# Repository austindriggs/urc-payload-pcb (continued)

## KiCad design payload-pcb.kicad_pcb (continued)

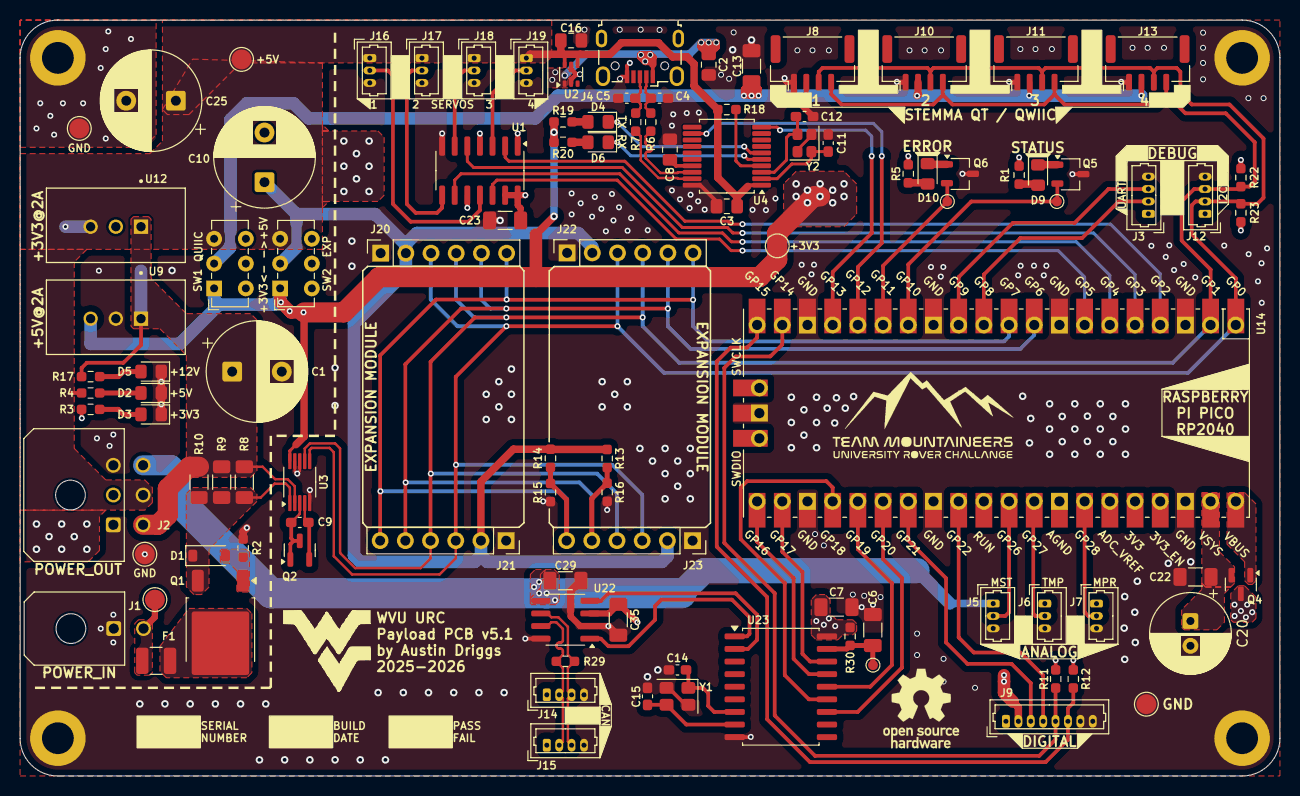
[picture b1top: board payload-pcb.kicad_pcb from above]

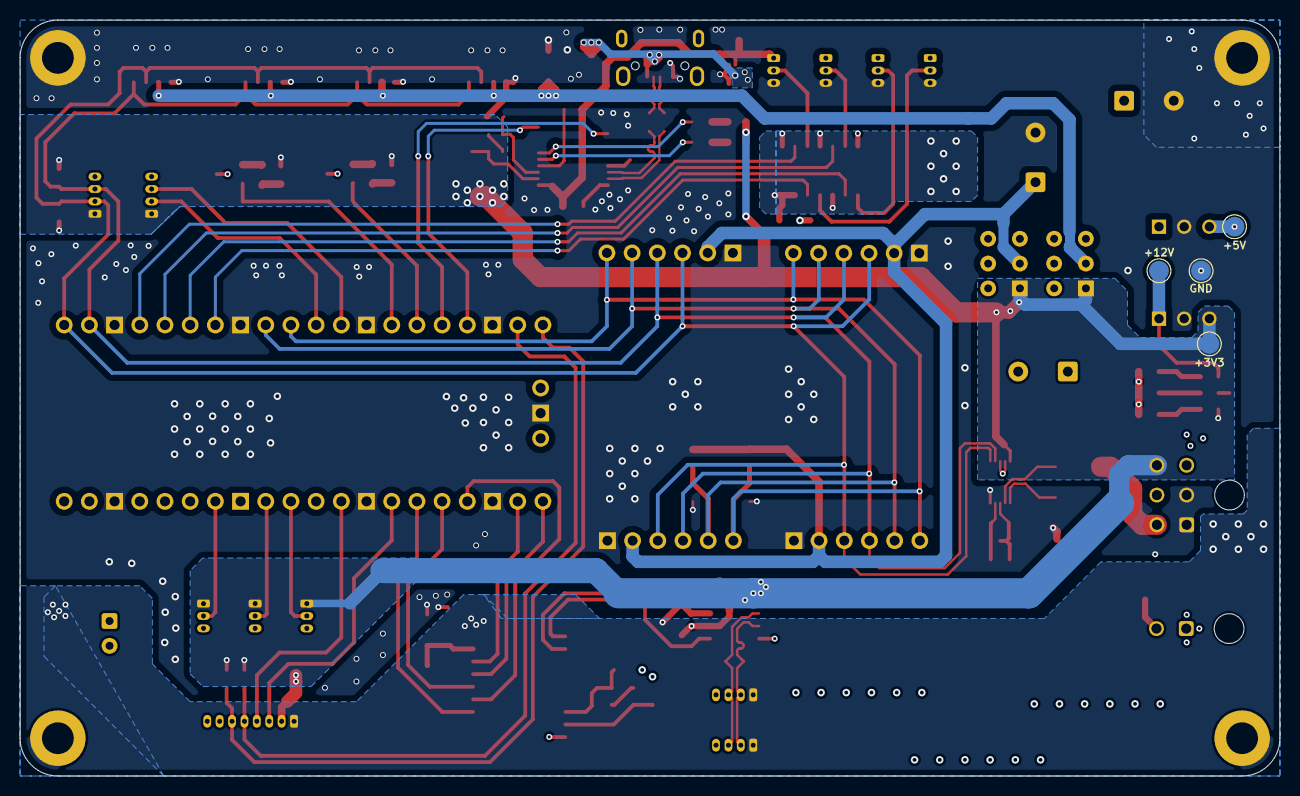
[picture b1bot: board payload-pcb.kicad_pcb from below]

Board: 4 copper layers, 127.0 x 76.2 mm, 113 parts (4 on the bottom side), 71 nets.

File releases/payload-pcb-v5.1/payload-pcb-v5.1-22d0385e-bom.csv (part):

"Reference","Value","DNP","Footprint","Datasheet","Description","Vendor","Vendor Part Number","Manufacturer","Manufacturer Part Number","Qty","Notes","Comments"
"C1,C10,C25","1000uF","","Capacitor_THT:CP_Radial_D10.0mm_P5.00mm","https://www.nichicon.co.jp/english/series_items/catalog_pdf/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","CAP ALUM 1000UF 20% 25V RADIAL","Digikey","493-1065-ND","Nichicon","UVR1E102MPD","3","",""
"C2,C3,C6,C7,C8,C22,C23,C29,C35","0.1uF","","Capacitor_SMD:C_1206_3216Metric_Pad1.33x1.80mm_HandSolder","https://www.yageogroup.com/content/datasheet/asset/file/KEM_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","CAP CER 0.1UF 50V X7R 1206","Digikey","399-C1206C104J5RACTUCT-ND","KEMET","C1206C104J5RACTU","9","",""
"C4,C5","47p","","Capacitor_SMD:C_0603_1608Metric_Pad1.08x0.95mm_HandSolder","https://www.yageogroup.com/content/datasheet/asset/file/KEM_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","CAP CER 47PF 50V X7R 0603","Digikey","399-C0603C470K5RACTUCT-ND","KEMET","C0603C470K5RACTU","2","",""
"C9","470pF","","Capacitor_SMD:C_0603_1608Metric_Pad1.08x0.95mm_HandSolder","https://www.yageogroup.com/content/datasheet/asset/file/KEM_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","CAP CER 470PF 50V X7R 0603","Digikey","399-C0603C471K5RACTUCT-ND","KEMET","C0603C471K5RACTU","1","",""
"C20","10uF","","Capacitor_THT:CP_Radial_D8.0mm_P2.50mm","https://www.nichicon.co.jp/english/series_items/catalog_pdf/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","CAP ALUM 10UF 20% 160V RADIAL TH","Digikey","493-12828-1-ND","Nichicon","UVR2C100MPD1TD","1","",""
"C30,C31","22pF","","Capacitor_SMD:C_0603_1608Metric_Pad1.08x0.95mm_HandSolder","https://www.yageogroup.com/content/datasheet/asset/file/KEM_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","CAP CER 22PF 50V X7R 0603","Digikey","399-C0603C220K5RACTUCT-ND","KEMET","C0603C220K5RACTU","2","",""
"D1","BZT52C10-TP","","Diode_SMD:D_SOD-123","https://www.mccsemi.com/pdf/Products/BZT52C2V0_BZT52C75(500m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","DIODE ZENER 10V 500MW SOD123","Digikey","BZT52C10-TPMSCT-ND","MCC (Micro Commercial Components)","BZT52C10-TP","1","",""
"D2","+5V","","LED_SMD:LED_0805_2012Metric_Pad1.15x1.40mm_HandSolder","https://www.we-online.com/components/products/datasheet/1500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","LED GREEN CLEAR 0805 SMD","Digikey","732-4983-1-ND","Würth Elektronik","150080GS75000","1","",""
"D3","+3V3","","LED_SMD:LED_0805_2012Metric_Pad1.15x1.40mm_HandSolder","https://www.we-online.com/components/products/datasheet/1500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","LED GREEN CLEAR 0805 SMD","Digikey","732-4983-1-ND","Würth Elektronik","150080GS75000","1","",""
"D5","+12V","","LED_SMD:LED_0805_2012Metric_Pad1.15x1.40mm_HandSolder","https://www.we-online.com/components/products/datasheet/1500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","LED GREEN CLEAR 0805 SMD","Digikey","732-4983-1-ND","Würth Elektronik","150080GS75000","1","",""
"D9","STATUS","","LED_SMD:LED_0805_2012Metric_Pad1.15x1.40mm_HandSolder","https://www.we-online.com/components/products/datasheet/1500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","LED BLUE CLEAR 0805 SMD","Digikey","732-4982-1-ND","Würth Elektronik","150080BS75000","1","",""
"D10","ERROR","","LED_SMD:LED_0805_2012Metric_Pad1.15x1.40mm_HandSolder","https://www.we-online.com/components/products/datasheet/1500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","LED RED CLEAR 0805 SMD","Digikey","732-4984-1-ND","Würth Elektronik","150080RS75000","1","",""
"F1","PTC","","Fuse:Fuse_1210_3225Metric","https://www.littelfuse.com/assetdocs/1210l-datasheet-update?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","PTC RESET FUSE 16V 1.5A 1210","Digikey","F6135CT-ND","Littelfuse Inc.","1210L150/16WR","1","",""
"H1,H2,H3,H4","MountingHole","","MountingHole:MountingHole_3.2mm_M3_DIN965_Pad","~","","","","","","4","",""
"J1","POWER_IN","","Connector_Molex:Molex_Micro-Fit_3.0_43045-0200_2x01_P3.00mm_Horizontal","https://tools.molex.com/pdm_docs/ps/PS-43045.pdf","CONN HEADER R/A 2POS","Digikey","WM1813-ND","Molex","0430450200","1","",""
"J2","POWER_OUT","","Connector_Molex:Molex_Micro-Fit_3.0_43045-0600_2x03_P3.00mm_Horizontal","https://tools.molex.com/pdm_docs/ps/PS-43045.pdf","CONN HEADER R/A 6POS 3MM","Digikey","WM1821-ND","Molex","0430450602","1","",""
"J3","UART","DNP","Connector_Molex:Molex_PicoBlade_53047-0410_1x04_P1.25mm_Vertical","https://www.molex.com/pdm_docs/sd/530470310_sd.pdf","CONN HEADER VERT 4POS 1.25MM","Digikey","WM1733-ND","Molex","0530470410","1","",""
"J4","USB","","Connector_USB:USB_Micro-B_Wuerth_629105150521","https://www.we-online.com/components/products/datasheet/6291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","CONN RCPT USB2.0 MICRO B SMD R/A","Digikey","732-5960-1-ND","Würth Elektronik","629105150521","1","",""
"J5","MST","","Connector_Molex:Molex_PicoBlade_53047-0310_1x03_P1.25mm_Vertical","https://www.molex.com/pdm_docs/sd/530470310_sd.pdf","CONN HEADER VERT 3POS 1.25MM","Digikey","WM1732-ND","Molex","0530470310","1","",""
"J6","TMP","","Connector_Molex:Molex_PicoBlade_53047-0310_1x03_P1.25mm_Vertical","https://www.molex.com/pdm_docs/sd/530470310_sd.pdf","CONN HEADER VERT 3POS 1.25MM","Digikey","WM1732-ND","Molex","0530470310","1","",""
"J7","MPR","","Connector_Molex:Molex_PicoBlade_53047-0310_1x03_P1.25mm_Vertical","https://www.molex.com/pdm_docs/sd/530470310_sd.pdf","CONN HEADER VERT 3POS 1.25MM","Digikey","WM1732-ND","Molex","0530470310","1","",""
"J8","QWIIC4","","Connector_JST:JST_GH_BM04B-GHS-TBT_1x04-1MP_P1.25mm_Vertical","https://www.jst-mfg.com/product/pdf/eng/eGH.pdf","CONN HEADER SMD R/A 4POS 1.25MM","Digikey","SM04B-GHS-TB","JST Sales America Inc.","455-1566-1-ND","1","",""
"J9","DIGITAL","","Connector_Molex:Molex_PicoBlade_53047-0810_1x08_P1.25mm_Vertical","https://www.molex.com/pdm_docs/sd/530470310_sd.pdf","CONN HEADER VERT 8POS 1.25MM","Digikey","WM1737-ND","Molex","0530470810","1","",""
"J10","QWIIC3","","Connector_JST:JST_GH_BM04B-GHS-TBT_1x04-1MP_P1.25mm_Vertical","https://www.jst-mfg.com/product/pdf/eng/eGH.pdf","CONN HEADER SMD R/A 4POS 1.25MM","Digikey","SM04B-GHS-TB","JST Sales America Inc.","455-1566-1-ND","1","",""
"J11","QWIIC2","","Connector_JST:JST_GH_BM04B-GHS-TBT_1x04-1MP_P1.25mm_Vertical","https://www.jst-mfg.com/product/pdf/eng/eGH.pdf","CONN HEADER SMD R/A 4POS 1.25MM","Digikey","SM04B-GHS-TB","JST Sales America Inc.","455-1566-1-ND","1","",""
"J12","I2C","DNP","Connector_Molex:Molex_PicoBlade_53047-0410_1x04_P1.25mm_Vertical","https://www.molex.com/pdm_docs/sd/530470310_sd.pdf","CONN HEADER VERT 4POS 1.25MM","Digikey","WM1733-ND","Molex","0530470410","1","",""
"J13","QWIIC1","","Connector_JST:JST_GH_BM04B-GHS-TBT_1x04-1MP_P1.25mm_Vertical","https://www.jst-mfg.com/product/pdf/eng/eGH.pdf","CONN HEADER SMD R/A 4POS 1.25MM","Digikey","SM04B-GHS-TB","JST Sales America Inc.","455-1566-1-ND","1","",""
"J14,J15","CAN","","Connector_Molex:Molex_PicoBlade_53047-0410_1x04_P1.25mm_Vertical","https://www.molex.com/pdm_docs/sd/530470310_sd.pdf","CONN HEADER VERT 4POS 1.25MM","Digikey","WM1733-ND","Molex","0530470410","2","",""
"J16","SERVO4","","Connector_Molex:Molex_PicoBlade_53047-0310_1x03_P1.25mm_Vertical","https://www.molex.com/pdm_docs/sd/530470310_sd.pdf","CONN HEADER VERT 3POS 1.25MM","Digikey","WM1732-ND","Molex","0530470310","1","",""
"J17","SERVO3","","Connector_Molex:Molex_PicoBlade_53047-0310_1x03_P1.25mm_Vertical","https://www.molex.com/pdm_docs/sd/530470310_sd.pdf","CONN HEADER VERT 3POS 1.25MM","Digikey","WM1732-ND","Molex","0530470310","1","",""
"J18","MANIPULATOR","","Connector_Molex:Molex_PicoBlade_53047-0310_1x03_P1.25mm_Vertical","https://www.molex.com/pdm_docs/sd/530470310_sd.pdf","CONN HEADER VERT 3POS 1.25MM","Digikey","WM1732-ND","Molex","0530470310","1","",""
"J19","SCOOP","","Connector_Molex:Molex_PicoBlade_53047-0310_1x03_P1.25mm_Vertical","https://www.molex.com/pdm_docs/sd/530470310_sd.pdf","CONN HEADER VERT 3POS 1.25MM","Digikey","WM1732-ND","Molex","0530470310","1","",""
"J20","EXP1","","Connector_PinSocket_2.54mm:PinSocket_1x06_P2.54mm_Vertical","https://mm.digikey.com/Volume0/opasdata/d220001/medias/docus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","CONN RCPT 6POS 0.1 GOLD PCB","Digikey","SAM10025-ND","Samtec Inc.","SAM10025-ND","1","",""
"J21","EXP2","","Connector_PinSocket_2.54mm:PinSocket_1x06_P2.54mm_Vertical","https://mm.digikey.com/Volume0/opasdata/d220001/medias/docus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","CONN RCPT 6POS 0.1 GOLD PCB","Digikey","SAM10025-ND","Samtec Inc.","SAM10025-ND","1","",""
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
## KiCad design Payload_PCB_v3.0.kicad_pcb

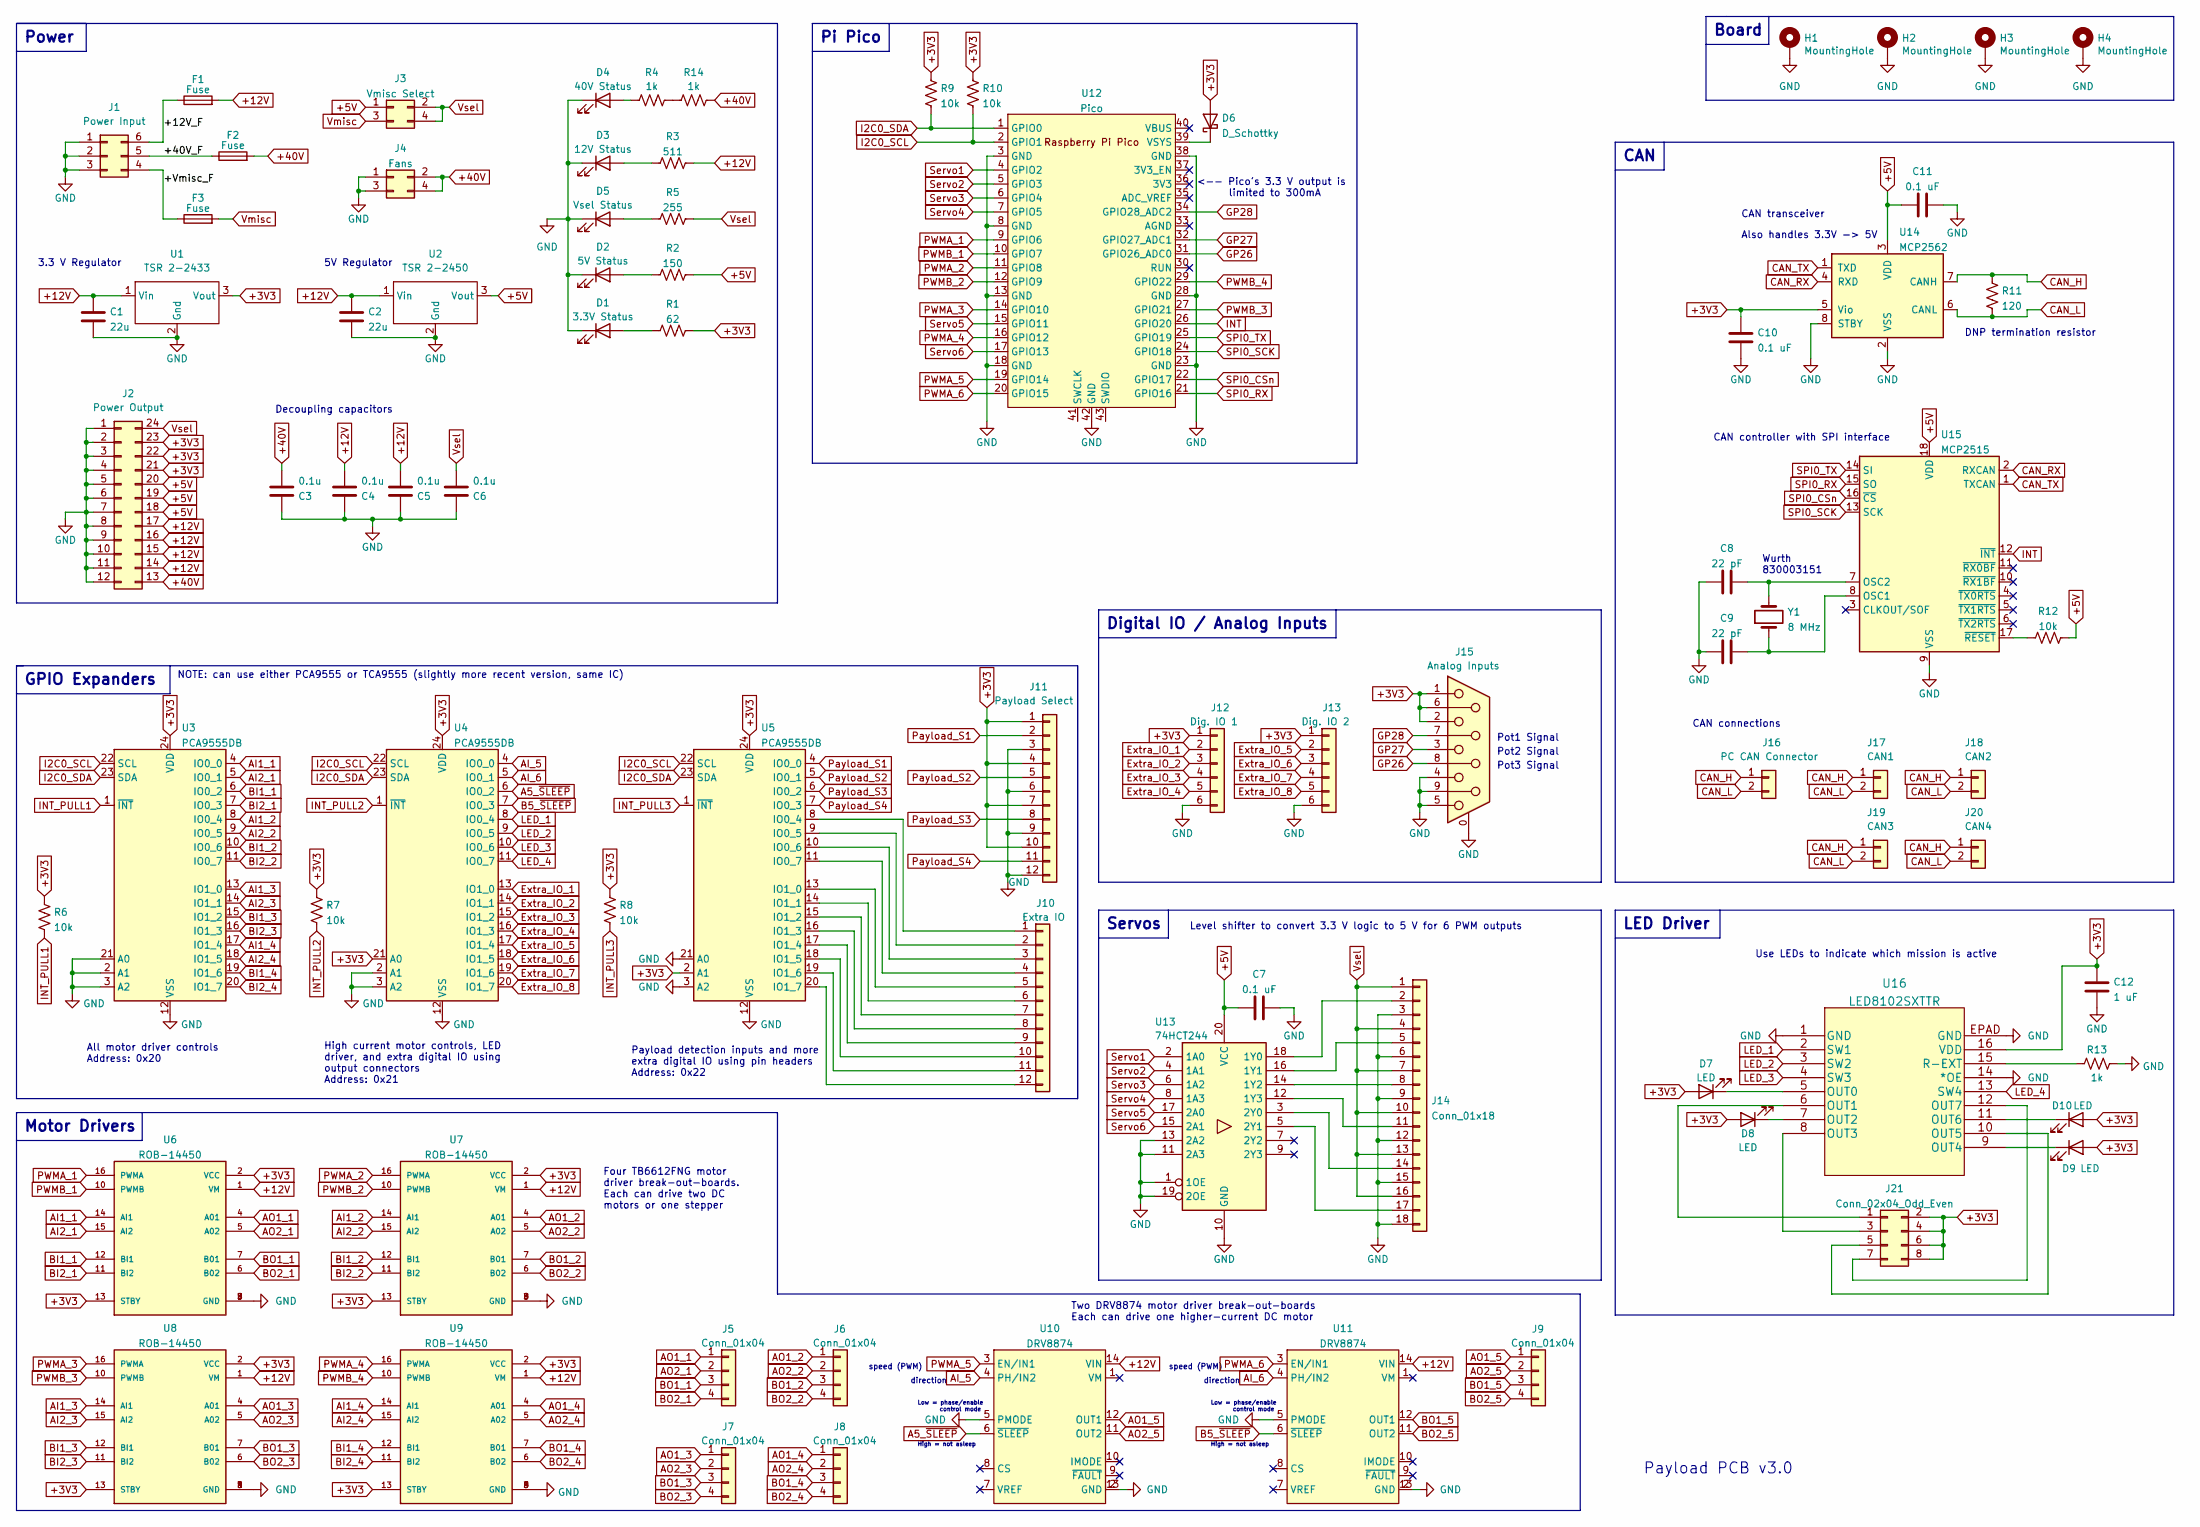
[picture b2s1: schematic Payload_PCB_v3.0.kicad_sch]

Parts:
C1, C2: 22u; UCM1H220MCL1GS
C3, C4, C5, C6: 0.1u; C_1206_3216Metric_Pad1.33x1.80mm_HandSolder
C7, C10, C11: 0.1 uF; C_1206_3216Metric_Pad1.33x1.80mm_HandSolder
C8, C9: 22 pF; C_0603_1608Metric_Pad1.08x0.95mm_HandSolder
C12: 1 uF; C_1206_3216Metric_Pad1.33x1.80mm_HandSolder
D1: 3.3V Status; LED_0805_2012Metric_Pad1.15x1.40mm_HandSolder
D2: 5V Status; LED_0805_2012Metric_Pad1.15x1.40mm_HandSolder
D3: 12V Status; LED_0805_2012Metric_Pad1.15x1.40mm_HandSolder
D4: 40V Status; LED_0805_2012Metric_Pad1.15x1.40mm_HandSolder
D5: Vsel Status; LED_0805_2012Metric_Pad1.15x1.40mm_HandSolder
D6: D_Schottky; D_SOD-323_HandSoldering
D7, D8, D9, D10: LED; LED_0805_2012Metric_Pad1.15x1.40mm_HandSolder
F1, F2, F3: Fuse; Fuseholder_Blade_Mini_Keystone_3568
H1, H2, H3, H4: MountingHole; MountingHole_3.2mm_M3_DIN965_Pad
J1: Power Input; Molex_Mini-Fit_Jr_5569-06A2_2x03_P4.20mm_Horizontal
J2: Power Output; Molex_Mini-Fit_Jr_5569-24A2_2x12_P4.20mm_Horizontal
J3: Vmisc Select; PinHeader_2x02_P2.54mm_Vertical
J4: Fans; PinHeader_2x02_P2.54mm_Vertical
J5, J6, J7, J8, J9: Conn_01x04; PhoenixContact_MCV_1,5_4-G-3.5_1x04_P3.50mm_Vertical
J10: Extra IO; PinSocket_2x06_P2.54mm_Vertical
J11: Payload Select; SAMTEC_TSW-104-07-T-T
J12: Dig. IO 1; Molex_PicoBlade_53048-0610_1x06_P1.25mm_Horizontal
J13: Dig. IO 2; Molex_PicoBlade_53048-0610_1x06_P1.25mm_Horizontal
J14: Conn_01x18; SAMTEC_TSW-106-07-S-T
J15: Analog Inputs; DSUB-9_Female_Horizontal_P2.77x2.84mm_EdgePinOffset7.70mm_H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
J16: PC CAN Connector; 0393570002
J17: CAN1; 0393570002
J18: CAN2; 0393570002
J19: CAN3; 0393570002
J20: CAN4; 0393570002
J21: Conn_02x04_Odd_Even; PinHeader_2x04_P2.54mm_Vertical_SMD
R1: 62; R_0805_2012Metric_Pad1.20x1.40mm_HandSolder
R2: 150; R_0805_2012Metric_Pad1.20x1.40mm_HandSolder
R3: 511; R_0805_2012Metric_Pad1.20x1.40mm_HandSolder
R4, R13, R14: 1k; R_0805_2012Metric_Pad1.20x1.40mm_HandSolder
R5: 255; R_0805_2012Metric_Pad1.20x1.40mm_HandSolder
R6, R7, R8, R9, R10, R12: 10k; R_0805_2012Metric_Pad1.20x1.40mm_HandSolder
R11: 120; R_Axial_DIN0207_L6.3mm_D2.5mm_P10.16mm_Horizontal
U1: TSR 2-2433; CONV_TSR_2-2433
U2: TSR 2-2450; CONV_TSR_2-2433
U3, U4, U5: PCA9555DB; SSOP-24_3.9x8.7mm_P0.635mm
U6, U7, U8, U9: ROB-14450; MODULE_ROB-14450; PARTREV 11-13-17
U10, U11: DRV8874
U12: Pico; RPi_Pico_SMD_TH
U13: 74HCT244; SO-20_12.8x7.5mm_P1.27mm
U14: MCP2562; SOIC-8_3.9x4.9mm_P1.27mm
U15: MCP2515; SOIC-18W_7.5x11.6mm_P1.27mm
U16: LED8102SXTTR
Y1: 8 MHz; Crystal_SMD_HC49-SD

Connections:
+3V3: C10.1, C12.1, D6.2 (A), D7.2 (A), D8.2 (A), D9.2 (A), D10.2 (A), J2.21, J2.22, J2.23, J11.1, J11.4, J11.7, J11.10, J12.1, J13.1, J15.1, J15.2, J15.6, J21.2, J21.4, J21.6, J21.8, R1.2, R6.2, R7.2, R8.2, R9.2, R10.2, U1.3 (Vout), U3.24 (VDD), U4.21 (A0), U4.24 (VDD), U5.2 (A1), U5.24 (VDD), U6.2 (VCC), U6.13 (STBY), U7.2 (VCC), U7.13 (STBY), U8.2 (VCC), U8.13 (STBY), U9.2 (VCC), U9.13 (STBY), U14.5 (Vio), U16.16 (VDD)
+5V: C7.1, C11.1, J2.18, J2.19, J2.20, J3.1, R2.2, R12.2, U2.3 (Vout), U13.20 (VCC), U14.3 (VDD), U15.18 (VDD)
+12V: C1.1, C2.1, C4.2, C5.2, F1.2, J2.14, J2.15, J2.16, J2.17, R3.2, U1.1 (Vin), U2.1 (Vin), U6.1 (VM), U7.1 (VM), U8.1 (VM), U9.1 (VM), U10.14 (VIN), U11.14 (VIN)
+40V: C3.2, F2.2, J2.13, J4.2, J4.4, R14.2
/+12V_F: F1.1, J1.6
/+40V_F: F2.1, J1.5
/+Vmisc_F: F3.1, J1.4
A5_~SLEEP: U4.6 (IO0_2), U10.6 (~SLEEP)
AI1_1: U3.4 (IO0_0), U6.14 (AI1)
AI1_2: U3.8 (IO0_4), U7.14 (AI1)
AI1_3: U3.13 (IO1_0), U8.14 (AI1)
AI1_4: U3.17 (IO1_4), U9.14 (AI1)
AI2_1: U3.5 (IO0_1), U6.15 (AI2)
AI2_2: U3.9 (IO0_5), U7.15 (AI2)
AI2_3: U3.14 (IO1_1), U8.15 (AI2)
AI2_4: U3.18 (IO1_5), U9.15 (AI2)
AI_5: U4.4 (IO0_0), U10.4 (PH/IN2)
AI_6: U4.5 (IO0_1), U11.4 (PH/IN2)
AO1_1: J5.1, U6.4 (A01)
AO1_2: J6.1, U7.4 (A01)
AO1_3: J7.1, U8.4 (A01)
AO1_4: J8.1, U9.4 (A01)
AO1_5: J9.1, U10.12 (OUT1)
AO2_1: J5.2, U6.5 (A02)
AO2_2: J6.2, U7.5 (A02)
AO2_3: J7.2, U8.5 (A02)
AO2_4: J8.2, U9.5 (A02)
AO2_5: J9.2, U10.11 (OUT2)
B5_~SLEEP: U4.7 (IO0_3), U11.6 (~SLEEP)
BI1_1: U3.6 (IO0_2), U6.12 (BI1)
BI1_2: U3.10 (IO0_6), U7.12 (BI1)
BI1_3: U3.15 (IO1_2), U8.12 (BI1)
BI1_4: U3.19 (IO1_6), U9.12 (BI1)
BI2_1: U3.7 (IO0_3), U6.11 (BI2)
BI2_2: U3.11 (IO0_7), U7.11 (BI2)
BI2_3: U3.16 (IO1_3), U8.11 (BI2)
BI2_4: U3.20 (IO1_7), U9.11 (BI2)
BO1_1: J5.3, U6.7 (B01)
BO1_2: J6.3, U7.7 (B01)
BO1_3: J7.3, U8.7 (B01)
BO1_4: J8.3, U9.7 (B01)
BO1_5: J9.3, U11.12 (OUT1)
BO2_1: J5.4, U6.6 (B02)
BO2_2: J6.4, U7.6 (B02)
BO2_3: J7.4, U8.6 (B02)
BO2_4: J8.4, U9.6 (B02)
BO2_5: J9.4, U11.11 (OUT2)
CAN_H: J16.1, J17.1, J18.1, J19.1, J20.1, R11.2, U14.7 (CANH)
CAN_L: J16.2, J17.2, J18.2, J19.2, J20.2, R11.1, U14.6 (CANL)
CAN_RX: U14.4 (RXD), U15.2 (RXCAN)
CAN_TX: U14.1 (TXD), U15.1 (TXCAN)
Extra_IO_1: J12.2, U4.13 (IO1_0)
Extra_IO_2: J12.3, U4.14 (IO1_1)
Extra_IO_3: J12.4, U4.15 (IO1_2)
Extra_IO_4: J12.5, U4.16 (IO1_3)
Extra_IO_5: J13.2, U4.17 (IO1_4)
Extra_IO_6: J13.3, U4.18 (IO1_5)
Extra_IO_7: J13.4, U4.19 (IO1_6)
Extra_IO_8: J13.5, U4.20 (IO1_7)
GND: C1.2, C2.2, C3.1, C4.1, C5.1, C6.1, C7.2, C8.1, C9.1, C10.2, C11.2, C12.2, D1.1 (K), D2.1 (K), D3.1 (K), D4.1 (K), D5.1 (K), H1.1, H2.1, H3.1, H4.1, J1.1, J1.2, J1.3, J2.1, J2.2, J2.3, J2.4, J2.5, J2.6, J2.7, J2.8, J2.9, J2.10, J2.11, J2.12, J4.1, J4.3, J11.3, J11.6, J11.9, J11.12, J12.6, J13.6, J14.3, J14.6, J14.9, J14.12, J14.15, J14.18, J15.0 (PAD), J15.4, J15.5, J15.9, R13.2, U1.2 (Gnd), U2.2 (Gnd), U3.2 (A1), U3.3 (A2), U3.12 (VSS), U3.21 (A0), U4.2 (A1), U4.3 (A2), U4.12 (VSS), U5.3 (A2), U5.12 (VSS), U5.21 (A0), U6.3 (GND), U6.8 (GND), U6.9 (GND), U7.3 (GND), U7.8 (GND), U7.9 (GND), U8.3 (GND), U8.8 (GND), U8.9 (GND), U9.3 (GND), U9.8 (GND), U9.9 (GND), U10.2 (GND), U10.5 (PMODE), U10.13 (GND), U11.2 (GND), U11.5 (PMODE), U11.13 (GND), U12.3 (GND), U12.8 (GND), U12.13 (GND), U12.18 (GND), U12.23 (GND), U12.28 (GND), U12.38 (GND), U12.42 (GND), U13.1 (1OE), U13.10 (GND), U13.11 (2A3), U13.13 (2A2), U13.19 (2OE), U14.2 (VSS), U14.8 (STBY), U15.9 (VSS), U16.1 (GND), U16.14 (*OE), U16.EPAD (GND)
GP26: J15.8, U12.31 (GPIO26_ADC0)
GP27: J15.3, U12.32 (GPIO27_ADC1)
GP28: J15.7, U12.34 (GPIO28_ADC2)
I2C0_SCL: R10.1, U3.22 (SCL), U4.22 (SCL), U5.22 (SCL), U12.2 (GPIO1)
I2C0_SDA: R9.1, U3.23 (SDA), U4.23 (SDA), U5.23 (SDA), U12.1 (GPIO0)
INT: U12.26 (GPIO20), U15.12 (~INT)
INT_PULL1: R6.1, U3.1 (~INT)
INT_PULL2: R7.1, U4.1 (~INT)
INT_PULL3: R8.1, U5.1 (~INT)
LED_1: U4.8 (IO0_4), U16.2 (SW1)
LED_2: U4.9 (IO0_5), U16.3 (SW2)
LED_3: U4.10 (IO0_6), U16.4 (SW3)
LED_4: U4.11 (IO0_7), U16.13 (SW4)
unnamed: C8.2, U15.7 (OSC2), Y1.2
unnamed: C9.2, U15.8 (OSC1), Y1.1
unnamed: D1.2 (A), R1.1
unnamed: D2.2 (A), R2.1
unnamed: D3.2 (A), R3.1
unnamed: D4.2 (A), R4.1
unnamed: D5.2 (A), R5.1
unnamed: D6.1 (K), U12.39 (VSYS)
unnamed: D7.1 (K), U16.5 (OUT0)
unnamed: D8.1 (K), U16.7 (OUT2)
unnamed: D9.1 (K), U16.9 (OUT4)
unnamed: D10.1 (K), U16.11 (OUT6)
unnamed: J10.1, U5.8 (IO0_4)
unnamed: J10.2, U5.9 (IO0_5)
unnamed: J10.3, U5.10 (IO0_6)
unnamed: J10.4, U5.11 (IO0_7)
unnamed: J10.5, U5.13 (IO1_0)
unnamed: J10.6, U5.14 (IO1_1)
unnamed: J10.7, U5.15 (IO1_2)
unnamed: J10.8, U5.16 (IO1_3)
unnamed: J10.9, U5.17 (IO1_4)
unnamed: J10.10, U5.18 (IO1_5)
unnamed: J10.11, U5.19 (IO1_6)
unnamed: J10.12, U5.20 (IO1_7)
unnamed: J14.2, U13.18 (1Y0)
unnamed: J14.5, U13.16 (1Y1)
unnamed: J14.8, U13.14 (1Y2)
unnamed: J14.11, U13.12 (1Y3)
unnamed: J14.14, U13.3 (2Y0)
unnamed: J14.17, U13.5 (2Y1)
unnamed: J21.1, U16.6 (OUT1)
unnamed: J21.3, U16.8 (OUT3)
unnamed: J21.5, U16.10 (OUT5)
unnamed: J21.7, U16.12 (OUT7)
unnamed: R12.1, U15.17 (~RESET)
unnamed: R13.1, U16.15 (R-EXT)
unnamed: R4.2, R14.1
PWMA_1: U6.16 (PWMA), U12.9 (GPIO6)
PWMA_2: U7.16 (PWMA), U12.11 (GPIO8)
PWMA_3: U8.16 (PWMA), U12.14 (GPIO10)
PWMA_4: U9.16 (PWMA), U12.16 (GPIO12)
PWMA_5: U10.3 (EN/IN1), U12.19 (GPIO14)
PWMA_6: U11.3 (EN/IN1), U12.20 (GPIO15)
PWMB_1: U6.10 (PWMB), U12.10 (GPIO7)
PWMB_2: U7.10 (PWMB), U12.12 (GPIO9)
PWMB_3: U8.10 (PWMB), U12.27 (GPIO21)
PWMB_4: U9.10 (PWMB), U12.29 (GPIO22)
Payload_S1: J11.2, U5.4 (IO0_0)
Payload_S2: J11.5, U5.5 (IO0_1)
Payload_S3: J11.8, U5.6 (IO0_2)
Payload_S4: J11.11, U5.7 (IO0_3)
SPI0_CSn: U12.22 (GPIO17), U15.16 (~CS)
SPI0_RX: U12.21 (GPIO16), U15.15 (SO)
SPI0_SCK: U12.24 (GPIO18), U15.13 (SCK)
SPI0_TX: U12.25 (GPIO19), U15.14 (SI)
Servo1: U12.4 (GPIO2), U13.2 (1A0)
Servo2: U12.5 (GPIO3), U13.4 (1A1)
Servo3: U12.6 (GPIO4), U13.6 (1A2)
Servo4: U12.7 (GPIO5), U13.8 (1A3)
Servo5: U12.15 (GPIO11), U13.17 (2A0)
Servo6: U12.17 (GPIO13), U13.15 (2A1)
Vmisc: F3.2, J3.3
Vsel: C6.2, J2.24, J3.2, J3.4, J14.1, J14.4, J14.7, J14.10, J14.13, J14.16, R5.2

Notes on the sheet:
speed (PWM)
<-- Pico's 3.3 V output is limited to 300mA
High = not asleep
CAN connections
Payload PCB v3.0
Four TB6612FNG motor driver break-out-boards. Each can drive two DC motors or one stepper
CAN transceiver
Wurth 830003151
Pot2 Signal
5V Regulator
Board
All motor driver controls Address: 0x20
DNP termination resistor
direction
Low = phase/enable control mode
Level shifter to convert 3.3 V logic to 5 V for 6 PWM outputs
GPIO Expanders
High current motor controls, LED driver, and extra digital IO using output connectors Address: 0x21
3.3 V Regulator
Payload detection inputs and more extra digital IO using pin headers Address: 0x22
CAN
Power
Pot3 Signal
CAN controller with SPI interface
Decoupling capacitors
Use LEDs to indicate which mission is active
Pi Pico
Digital IO / Analog Inputs
Servos
Pot1 Signal
Motor Drivers
NOTE: can use either PCA9555 or TCA9555 (slightly more recent version, same IC)
Also handles 3.3V -> 5V
LED Driver
Two DRV8874 motor driver break-out-boards Each can drive one higher-current DC motor

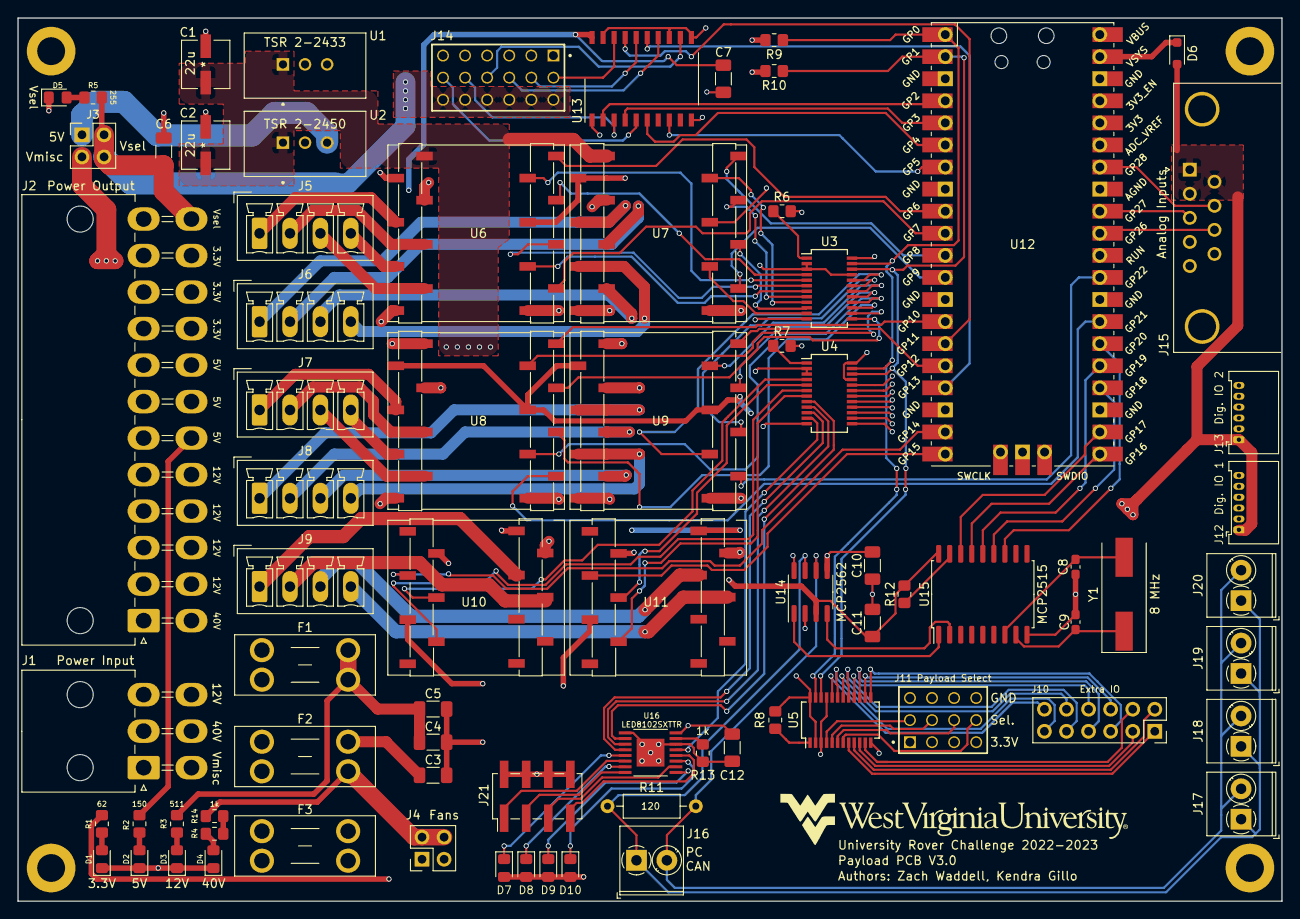
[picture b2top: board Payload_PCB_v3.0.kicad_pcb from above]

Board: 4 copper layers, 145.4 x 101.6 mm, 81 parts (0 on the bottom side), 136 nets.

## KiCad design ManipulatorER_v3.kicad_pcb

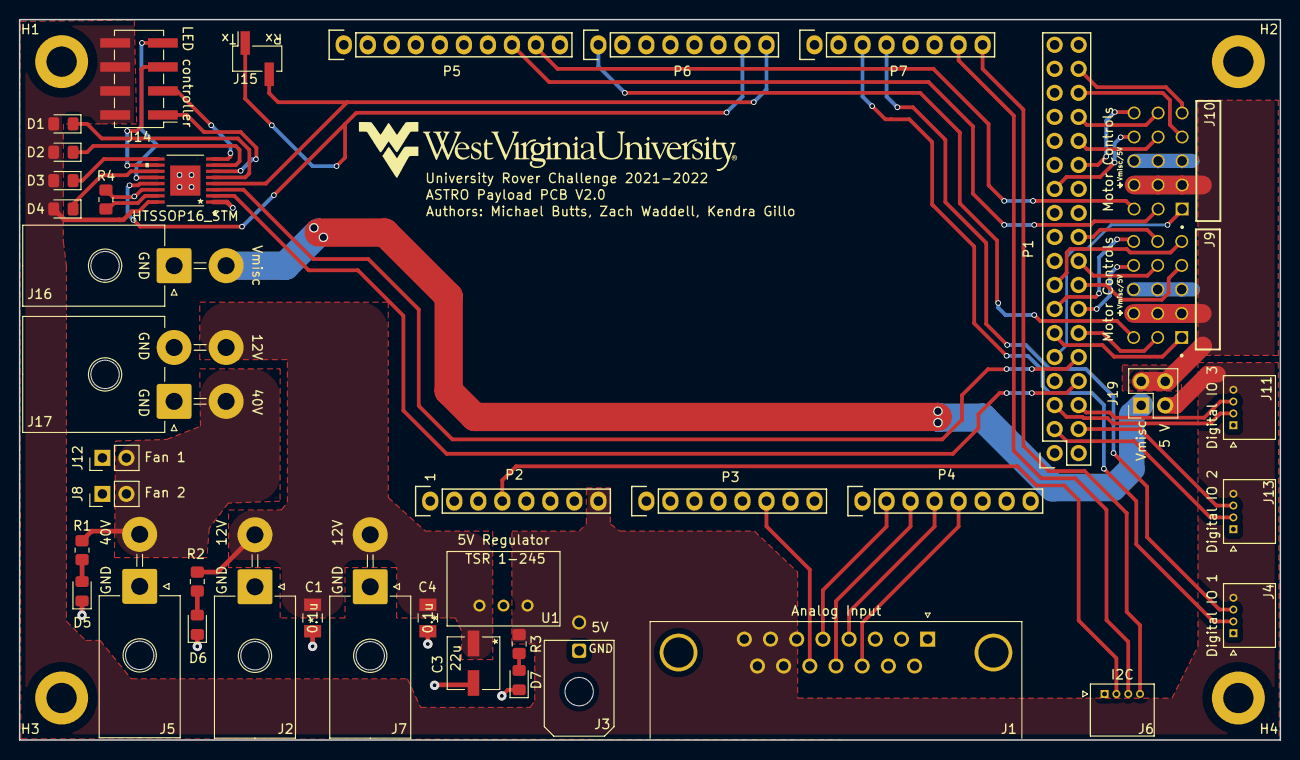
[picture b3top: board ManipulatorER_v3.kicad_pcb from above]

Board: 2 copper layers, 133.3 x 76.2 mm, 45 parts (0 on the bottom side), 42 nets.

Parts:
C1, C4: 0.1u; C1206C104J4RAC7800
C3: 22u; UCM1H220MCL1GS
D1, D2, D3, D4, D5, D6, D7: LED; LED_0805_2012Metric_Pad1.15x1.40mm_HandSolder
H1, H2, H3, H4: MountingHole; MountingHole_3.2mm_M3_DIN965_Pad
J1: DB15_Female_MountingHoles; DSUB-15_Female_Horizontal_P2.77x2.84mm_EdgePinOffset7.70mm_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
J2, J5, J7, J16: Conn_01x02; Molex_Mega-Fit_76825-0002_2x01_P5.70mm_Horizontal
J3: Conn_01x02; Molex_Micro-Fit_3.0_43045-0200_2x01_P3.00mm_Horizontal
J4, J6, J11, J13: Conn_01x04; MOLEX_530480410
J8, J12: Conn_01x02; PinHeader_1x02_P2.54mm_Vertical
J9, J10: Conn_01x15_Male; SAMTEC_TSW-105-08-G-T-RA
J14: Conn_02x04_Odd_Even; PinHeader_2x04_P2.54mm_Vertical_SMD
J15: Conn_01x02; PinHeader_1x02_P2.54mm_Vertical_SMD_Pin1Right
J17: Conn_02x02_Counter_Clockwise; Molex_Mega-Fit_76825-0004_2x02_P5.70mm_Horizontal
J19: Conn_02x02_Odd_Even; PinHeader_2x02_P2.54mm_Vertical
P1: Digital; Socket_Strip_Arduino_2x18
P2: Power; Socket_Strip_Arduino_1x08
P3, P4: Analog; Socket_Strip_Arduino_1x08
P5: PWM; Socket_Strip_Arduino_1x10
P6: PWM; Socket_Strip_Arduino_1x08
P7: Communication; Socket_Strip_Arduino_1x08
R1: 3000; R_0805_2012Metric_Pad1.20x1.40mm_HandSolder
R2: 750; R_0805_2012Metric_Pad1.20x1.40mm_HandSolder
R3: 150; R_0805_2012Metric_Pad1.20x1.40mm_HandSolder
R4: 976; R_0805_2012Metric_Pad1.20x1.40mm_HandSolder
U1: TSR 1-245; TSR 1-2433
U2: HTSSOP16_STM; LED8102SXTTR

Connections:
0(Rx0): J15.2, P6.8, U2.4 (SW3)
1(Tx0): J15.1, P6.7, U2.13 (SW4)
3V3: J6.2, P2.4
7(**): J9.03, P6.1
9(**): J10.03, P5.9
10(**): J10.02, P5.8
12V: C1.2, C3.1, C4.2, J2.2, J7.2, J17.4, R2.2, U1.1 (Vin)
16(Tx2): J4.2, P7.3
17(Rx2): J4.3, P7.4
20(SDA): J6.3, P7.7
21(SCL): J6.4, P7.8
23: J10.13, P1.34
25: J10.10, P1.32
27: J10.14, P1.30
29: J10.11, P1.28
31: J10.15, P1.26
32: J10.12, P1.23
37: J9.14, P1.20
39: J9.11, P1.18
40: J9.13, P1.15
40V: J5.2, J8.2, J12.2, J17.3, R1.2
41: J9.10, P1.16
42: J9.15, P1.13
43: J9.12, P1.14
44: J9.01, P1.11
45: J9.02, P1.12
46: J10.01, P1.9
47: P1.10, U2.3 (SW2)
49: P1.8, U2.2 (SW1)
50(MISO): J11.2, P1.5
51(MOSI): J11.3, P1.6
52(SCK): J13.2, P1.3
53(SS): J13.3, P1.4
+5V: D1.2 (A), D2.2 (A), D3.2 (A), D4.2 (A), J1.6, J1.7, J1.8, J1.14, J1.15, J3.2, J4.4, J11.4, J13.4, J14.2, J14.4, J14.6, J14.8, J19.3, P2.8, R3.2, U1.3 (Vout), U2.16 (VDD)
/+7V: J16.2, J19.1
A5: J1.13, P3.6
A9: J1.5, P4.2
A10: J1.12, P4.3
A11: J1.4, P4.4
A12: J1.11 (P111), P4.5
GND: C1.1, C3.2, C4.1, D5.1 (K), D6.1 (K), D7.1 (K), H1.1, H2.1, H3.1, H4.1, J1.0 (PAD), J1.1, J1.2, J1.3, J1.9, J1.10, J2.1, J3.1, J4.1, J5.1, J6.1, J7.1, J8.1, J9.07, J9.08, J9.09, J10.07, J10.08, J10.09, J11.1, J12.1, J13.1, J16.1, J17.1, J17.2, P1.1, P1.2, P2.6, P2.7, P5.4, R4.2, U1.2 (Gnd), U2.1 (GND), U2.14 (*OE), U2.EPAD (GND)
Vmisc: J9.04, J9.05, J9.06, J10.04, J10.05, J10.06, J19.2, J19.4

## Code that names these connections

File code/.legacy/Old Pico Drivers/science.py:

import machine
import onewire
import ds18x20
from machine import Pin, ADC
import lib.led as led

import lib.pwm as pwm

import time
import sys

from bme680 import BME680_I2C

bme = None

def init_bme680(i2c):
    global bme
    try:
        bme = BME680_I2C(i2c)
        sys.stdout.write("BME680 initialized\n")
    except Exception as e:
        sys.stdout.write(f"BME680 init failed: {e}\n")



def lin_act_init(pin: int):
    lin_act_pwm = machine.PWM(Pin(pin), freq = 50, duty_u16 = 0)
    return lin_act_pwm



#soil collector 1 servo will be on GPIO2 (physical pin 4) / SERVO1_PICO
#soil collector 2 servo will be on GPIO3 (physical pin 5) / SERVO2_PICO
def soil_collector_lin_act_init():
    return lin_act_init(2), lin_act_init(3)



#temperature and moisture probe, signal still needs to be like 5V RC control on GPIO4 (physical pin 6) / SERVO3_PICO
def probe_signal_init():
    return lin_act_init(4)



#drill actuator on GPIO5 (physical pin 7) / SERVO4_PICO
def drill_lin_act_init():
    return lin_act_init(5)



#Halogen bulb will be on GPIO22 (physical pin 29) / Digital_Relay2
def halogen_bulb_init():
    halogen_pin = Pin(22, Pin.OUT)
    halogen_pin.value(0)
    return halogen_pin



def moisture_sens_ADC_init():
    # GPIO26 (physical pin 31) / ADC0
    return ADC(Pin(26))



def temp_ow_init():
    # GPIO27 (physical pin 32) / ADC1
    return onewire.OneWire(Pin(27))



def temp_init(ow):
    return ds18x20.DS18X20(ow)



#Relay for the dynamixel control unit on GPIO21 (physical pin 27) / Digital_Relay1
def u2d2_relay_init():
    return Pin(21, Pin.OUT)



def timee(activeMaybe):
        if(activeMaybe == False):
            led.failure()
        else:
            activeMaybe = False



def temp_moist(moisture_adc, temp_sens):
    try:
        moisture_val = str(moisture_adc.read_u16())
        #After calling convert temp you need to give time for the sensor to actually convert its data
        temp_sens.convert_temp()
        temp_dev_id = temp_sens.scan()[0]
        time.sleep_ms(750)
        temperature = temp_sens.read_temp(temp_dev_id)
        sys.stdout.write(f"{moisture_val},{temperature}\n")
    except:
        return



def halogen_bulb_safety(halogen_pin, hb_active, hb_extender):
    if(hb_extender != 3):
        hb_extender = hb_extender + 1
        return
    else:
        halogen_pin.value(0)
        hb_active = False            



def input_flush(poll_obj):
    poll_result = poll_obj.poll(0)
    while (poll_result != []):
        poll_result = poll_obj.poll(0)
        dump = sys.stdin.readline()
    return







def mission(poll_obj, wdt, i2c):
    sys.stdout.write("Science!")
    activeMaybe = False
    
    soil_collector1_pwm, soil_collector2_pwm = soil_collector_lin_act_init()
    probe_pwm_signal = probe_signal_init()
    drill_pwm = drill_lin_act_init()
    halogen_pin = halogen_bulb_init()
    hb_extender = 0
    hb_active = False
    u2d2_pin = u2d2_relay_init()
    moisture_adc = moisture_sens_ADC_init()
    temp_ow = temp_ow_init()
    temp_sens = temp_init(temp_ow)


    pwm.set_pwm_duty(3300, soil_collector1_pwm)
    pwm.set_pwm_duty(3300, soil_collector2_pwm)
    pwm.set_pwm_duty(3300, probe_pwm_signal)
    pwm.set_pwm_duty(3630, drill_pwm)

    # emergencyTim = machine.Timer(-1)
    # emergencyTim.init(period = 100, mode = machine.Timer.PERIODIC, callback = lambda t: timee(activeMaybe))
    temp_moist_data_timer = machine.Timer(-1)
    temp_moist_data_timer.init(period = 4000, mode = machine.Timer.PERIODIC, callback = lambda t: temp_moist(moisture_adc, temp_sens))
    #hb_safety_timer = machine.Timer(period = 6500, mode = machine.Timer.PERIODIC, callback = halogen_bulb_safety(hb_active, hb_extender))
    input_flush_timer = machine.Timer(-1)
    input_flush_timer.init(period = 5000, mode = machine.Timer.PERIODIC, callback = lambda t: input_flush(poll_obj))
    
    while True:
        poll_result = poll_obj.poll(5)
        wdt.feed()
        if (poll_result == []):
            continue
        data = sys.stdin.readline().strip("\n")

        #science controls
        if(data == "sc1"):
            #led.value(1)
            data2 = sys.stdin.readline().strip("\n")
            try:
                duty = float(data2)
                pwm.set_pwm_duty((int(duty * 3300) + 3300), soil_collector1_pwm)
            except:
                continue

        elif(data == "sc2"):
            #led.value(1)
            data2 = sys.stdin.readline().strip("\n")
            try:
                duty = float(data2)
                pwm.set_pwm_duty((int(duty * 3300) + 3300), soil_collector2_pwm)
            except:
                continue

        elif(data == "probe"):
            #led.value(1)
            data2 = sys.stdin.readline().strip("\n")
            try:
                duty = float(data2)
                pwm.set_pwm_duty((int(duty * 3300) + 3300), probe_pwm_signal)
            except:
                continue

        #drill goes from 1.1 ms to 1.9 ms for retracted and extended instead of 1 ms and 2 ms like the other actuators
        elif(data == "drill"):
            #led.value(1)
            data2 = sys.stdin.readline().strip("\n")
            try:
                duty = float(data2)
                pwm.set_pwm_duty((int(duty * 2583) + 3630), drill_pwm)
            except:
                continue


        elif(data == "moist"):
            #led.value(1)
            moisture_val = str(moisture_adc.read_u16())
            sys.stdout.write(f"{moisture_val}\n")

        elif(data == "temp"):
            #led.value(1)
            #After calling convert temp you need to give time for the sensor to actually convert its data
            temp_sens.convert_temp()
            temp_dev_id = temp_sens.scan()
            time.sleep_ms(750)
            temperature = temp_sens.read_temp(temp_dev_id)
            sys.stdout.write(f"{temperature}\n")


        #halogen bulb control
        elif(data == "hbon"):
            if(hb_active == True):
                continue
            hb_active = True
            halogen_pin.value(1)
            hb_safety_timer = machine.Timer(-1)
            hb_safety_timer.init(period = 6500, mode = machine.Timer.ONE_SHOT, callback = halogen_bulb_safety(halogen_pin, hb_active, hb_extender))
    
        elif(data== "hboff"):
            hb_active = False
            halogen_pin.value(0)

        #u2d2 relay stuff goes here
        elif(data == "u2d2on"):
            #led.value(1)
            u2d2_pin.value(0)
    
        elif(data== "u2d2off"):
            #led.value(0)
            u2d2_pin.value(1)


        elif(data == "bme680"):
            if bme:
                temp = bme.temperature
                hum = bme.humidity
                pres = bme.pressure
                gas = bme.gas
                sys.stdout.write(f"Temperature: {temp:.2f} C, Humidity: {hum:.2f} %, Pressure: {pres:.2f} hPa, Gas: {gas} ohms\n")
            else:
                sys.stdout.write("BME680 not initialized\n")

        elif(data=='reset'):
            machine.reset()

        else:
            #led.value(0)
            continue

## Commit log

2025-10-07 payload pcb v1.0
2025-10-07 payload pcb v2.0
2025-10-07 payload pcb v3.0
2025-10-07 payload pcb v3.1
2025-11-13 updated gitignore
2025-11-13 initial cleanup of repo
2025-12-03 major, major rework for v5.0 and pdr
2025-12-03 more cleanup and added notes for review
2025-12-03 add gitignore
2025-12-03 DNP unused connectors for now
2025-12-03 pcb review session notes
2025-12-04 major rework again after the meeting
2026-01-03 major finishing touches: - major rework for v5.1 - silkscreen and stuff - impednace for USB and CAN lines - schematic comments - symbol, footprint, and model library updates
2026-01-03 removed unnecessary files
2026-01-03 moved gerbers to releases
2026-01-03 added support
2026-01-03 some repo cleanup
2026-01-03 some more docs. updated pico VPN to CT
2026-01-03 cropped images and changed files to .md
2026-01-03 generated gerbers for v5.1
2026-01-03 swapped UART to USB from FTDI (out of stock) to MCP2200
2026-01-03 added release documents for v5.1 (pending approval)
2026-01-11 touch ups from peer reviews
2026-01-13 updated some release files for v5.1
2026-01-13 updated rest of release files
2026-01-13 updated assembly pdf page names
2026-01-13 updated release files, bom, and jlc file
2026-01-16 Added housing/cable/header info to each connector's symbol properties.
2026-01-16 Imported connector info to PCB layout.
2026-01-16 Updated net class grouping and colors.
2026-01-16 README cleanup
2026-01-16 schematic cleanup
2026-03-20 updated readme and images after sar
2026-03-20 test github badges
2026-03-20 added github badges
2026-04-15 added images in support
2026-04-21 added code from urc
2026-05-08 backup of refs from laptop on 2026-04-08
